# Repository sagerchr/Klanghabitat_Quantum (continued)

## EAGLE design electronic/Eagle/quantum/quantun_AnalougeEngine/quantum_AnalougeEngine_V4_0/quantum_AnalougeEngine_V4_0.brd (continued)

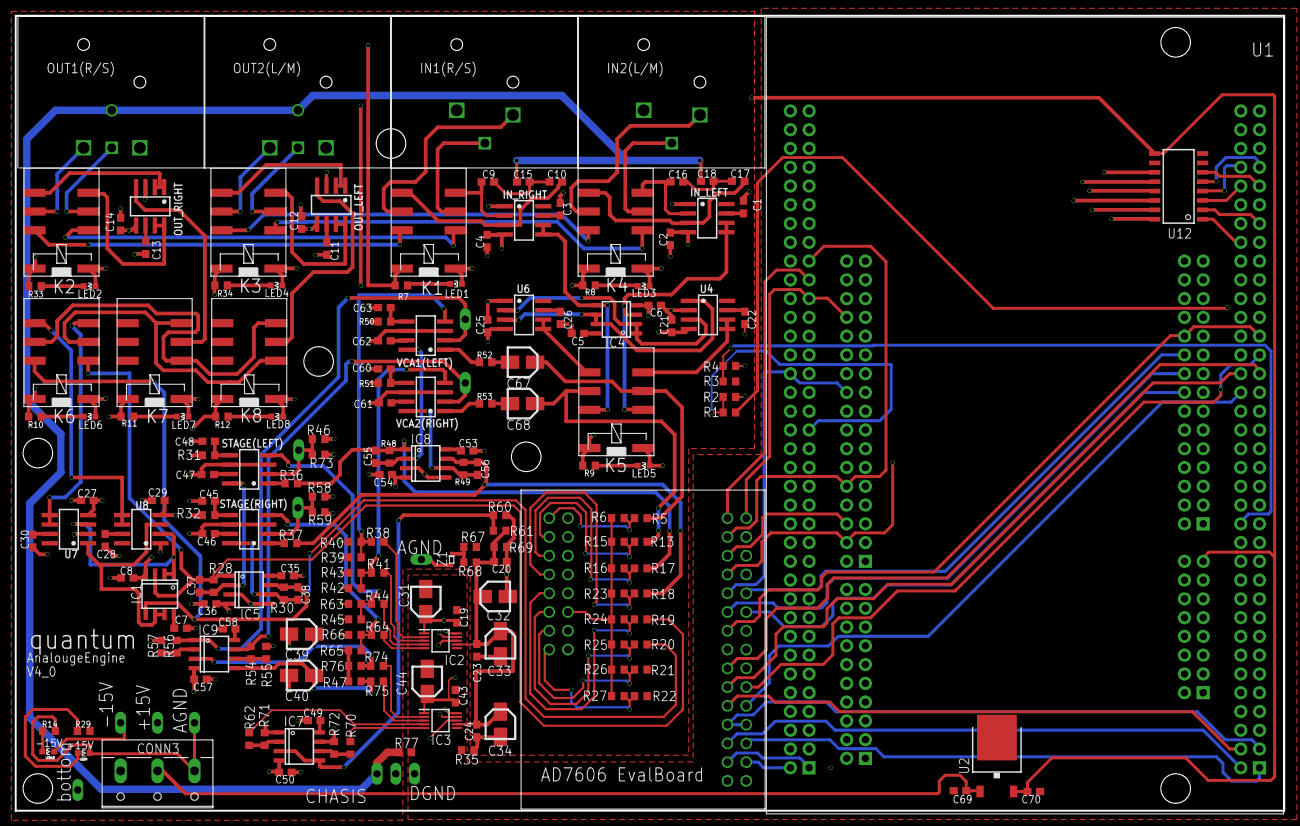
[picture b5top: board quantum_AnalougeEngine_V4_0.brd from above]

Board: 4 copper layers, 171.7 x 107.6 mm, 199 parts (0 on the bottom side), 155 nets.

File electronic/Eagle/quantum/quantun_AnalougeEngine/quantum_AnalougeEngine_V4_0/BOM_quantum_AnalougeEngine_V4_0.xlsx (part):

BOM_quantum_AnalougeEngine_V4_0
BOM_quantum_AnalougeEngine_V4_0
Part | Value | Device | Package | Description | MOUSER_PART_NUMBER | comments
U2 | 7812 | voltage regulator | TO252 |  | 513-NJM7812DL1A-TE1
R35 | 0R | RESISTOR | R0603 | +/- 5 % resistor
R77 | 0R | RESISTOR | R0603 | +/- 5 % resistor
C31 | 10 µF | ELECTROLYTICELCTROLYTIC_MIDSIZE_SMD | CAPAE400X550N | Electrolytic Capacitor SMD
C32 | 10 µF | ELECTROLYTICELCTROLYTIC_MIDSIZE_SMD | CAPAE400X550N | Electrolytic Capacitor SMD
C33 | 10 µF | ELECTROLYTICELCTROLYTIC_MIDSIZE_SMD | CAPAE400X550N | Electrolytic Capacitor SMD
C34 | 10 µF | ELECTROLYTICELCTROLYTIC_MIDSIZE_SMD | CAPAE400X550N | Electrolytic Capacitor SMD
C39 | 10 µF | ELECTROLYTICELCTROLYTIC_MIDSIZE_SMD | CAPAE400X550N | Electrolytic Capacitor SMD
C40 | 10 µF | ELECTROLYTICELCTROLYTIC_MIDSIZE_SMD | CAPAE400X550N | Electrolytic Capacitor SMD
C44 | 10 µF | ELECTROLYTICELCTROLYTIC_MIDSIZE_SMD | CAPAE400X550N | Electrolytic Capacitor SMD
C69 | 100 nF | CAPACITOR";C0603" | capacitor 0603 | ceremic capicitor
R2 | 100k | RESISTOR | R0603 | +/- 5 % resistor
R3 | 100k | RESISTOR | R0603 | +/- 5 % resistor
C1 | 100nF | CAPACITOR";C0603" | capacitor 0603 | ceremic capicitor
C11 | 100nF | CAPACITOR";C0603" | capacitor 0603 | ceremic capicitor
C12 | 100nF | CAPACITOR";C0603" | capacitor 0603 | ceremic capicitor
C13 | 100nF | CAPACITOR";C0603" | capacitor 0603 | ceremic capicitor
C14 | 100nF | CAPACITOR";C0603" | capacitor 0603 | ceremic capicitor
C19 | 100nF | CAPACITOR";C0603" | capacitor 0603 | ceremic capicitor
C2 | 100nF | CAPACITOR";C0603" | capacitor 0603 | ceremic capicitor
C20 | 100nF | CAPACITOR";C0603" | capacitor 0603 | ceremic capicitor
C21 | 100nF | CAPACITOR";C0603" | capacitor 0603 | ceremic capicitor
C22 | 100nF | CAPACITOR";C0603" | capacitor 0603 | ceremic capicitor
C23 | 100nF | CAPACITOR";C0603" | capacitor 0603 | ceremic capicitor
C24 | 100nF | CAPACITOR";C0603" | capacitor 0603 | ceremic capicitor
C25 | 100nF | CAPACITOR";C0603" | capacitor 0603 | ceremic capicitor
C26 | 100nF | CAPACITOR";C0603" | capacitor 0603 | ceremic capicitor
C27 | 100nF | CAPACITOR";C0603" | capacitor 0603 | ceremic capicitor
C28 | 100nF | CAPACITOR";C0603" | capacitor 0603 | ceremic capicitor
C29 | 100nF | CAPACITOR";C0603" | capacitor 0603 | ceremic capicitor
C3 | 100nF | CAPACITOR";C0603" | capacitor 0603 | ceremic capicitor
C30 | 100nF | CAPACITOR";C0603" | capacitor 0603 | ceremic capicitor
C35 | 100nF | CAPACITOR";C0603" | capacitor 0603 | ceremic capicitor
C36 | 100nF | CAPACITOR";C0603" | capacitor 0603 | ceremic capicitor
C4 | 100nF | CAPACITOR";C0603" | capacitor 0603 | ceremic capicitor
C43 | 100nF | CAPACITOR";C0603" | capacitor 0603 | ceremic capicitor
C45 | 100nF | CAPACITOR";C0603" | capacitor 0603 | ceremic capicitor
C46 | 100nF | CAPACITOR";C0603" | capacitor 0603 | ceremic capicitor
C47 | 100nF | CAPACITOR";C0603" | capacitor 0603 | ceremic capicitor
C48 | 100nF | CAPACITOR";C0603" | capacitor 0603 | ceremic capicitor
C49 | 100nF | CAPACITOR";C0603" | capacitor 0603 | ceremic capicitor
C5 | 100nF | CAPACITOR";C0603" | capacitor 0603 | ceremic capicitor
C50 | 100nF | CAPACITOR";C0603" | capacitor 0603 | ceremic capicitor
C53 | 100nF | CAPACITOR";C0603" | capacitor 0603 | ceremic capicitor
C54 | 100nF | CAPACITOR";C0603" | capacitor 0603 | ceremic capicitor
C57 | 100nF | CAPACITOR";C0603" | capacitor 0603 | ceremic capicitor
C58 | 100nF | CAPACITOR";C0603" | capacitor 0603 | ceremic capicitor
C6 | 100nF | CAPACITOR";C0603" | capacitor 0603 | ceremic capicitor
C60 | 100nF | CAPACITOR";C0603" | capacitor 0603 | ceremic capicitor
C61 | 100nF | CAPACITOR";C0603" | capacitor 0603 | ceremic capicitor
C62 | 100nF | CAPACITOR";C0603" | capacitor 0603 | ceremic capicitor
C63 | 100nF | CAPACITOR";C0603" | capacitor 0603 | ceremic capicitor
C7 | 100nF | CAPACITOR";C0603" | capacitor 0603 | ceremic capicitor
C8 | 100nF | CAPACITOR";C0603" | capacitor 0603 | ceremic capicitor
R1 | 10k | RESISTOR | R0603 | +/- 5 % resistor
R13 | 10k | RESISTOR | R0603 | +/- 5 % resistor
R15 | 10k | RESISTOR | R0603 | +/- 5 % resistor
R16 | 10k | RESISTOR | R0603 | +/- 5 % resistor
R17 | 10k | RESISTOR | R0603 | +/- 5 % resistor
R18 | 10k | RESISTOR | R0603 | +/- 5 % resistor
R19 | 10k | RESISTOR | R0603 | +/- 5 % resistor
R20 | 10k | RESISTOR | R0603 | +/- 5 % resistor
R21 | 10k | RESISTOR | R0603 | +/- 5 % resistor
R22 | 10k | RESISTOR | R0603 | +/- 5 % resistor
R23 | 10k | RESISTOR | R0603 | +/- 5 % resistor
R24 | 10k | RESISTOR | R0603 | +/- 5 % resistor
R25 | 10k | RESISTOR | R0603 | +/- 5 % resistor
R26 | 10k | RESISTOR | R0603 | +/- 5 % resistor
R27 | 10k | RESISTOR | R0603 | +/- 5 % resistor
R4 | 10k | RESISTOR | R0603 | +/- 5 % resistor
R46 | 10k | RESISTOR | R0603 | +/- 5 % resistor
R5 | 10k | RESISTOR | R0603 | +/- 5 % resistor
R54 | 10k | RESISTOR | R0603 | +/- 5 % resistor
R55 | 10k | RESISTOR | R0603 | +/- 5 % resistor
R56 | 10k | RESISTOR | R0603 | +/- 5 % resistor
R57 | 10k | RESISTOR | R0603 | +/- 5 % resistor
R58 | 10k | RESISTOR | R0603 | +/- 5 % resistor
R6 | 10k | RESISTOR | R0603 | +/- 5 % resistor
R60 | 10k | RESISTOR | R0603 | +/- 5 % resistor
R61 | 10k | RESISTOR | R0603 | +/- 5 % resistor
R62 | 10k | RESISTOR | R0603 | +/- 5 % resistor
R67 | 10k | RESISTOR | R0603 | +/- 5 % resistor
R68 | 10k | RESISTOR | R0603 | +/- 5 % resistor
R69 | 10k | RESISTOR | R0603 | +/- 5 % resistor
R70 | 10k | RESISTOR | R0603 | +/- 5 % resistor
R71 | 10k | RESISTOR | R0603 | +/- 5 % resistor
R72 | 10k | RESISTOR | R0603 | +/- 5 % resistor
R73 | 10k | RESISTOR | R0603 | +/- 5 % resistor
R74 | 10k | RESISTOR | R0603 | +/- 5 % resistor
R75 | 10k | RESISTOR | R0603 | +/- 5 % resistor
R47 | 1k8 | RESISTOR | R0603 | +/- 5 % resistor
R76 | 1k8 | RESISTOR | R0603 | +/- 5 % resistor
R28 | 20k | RESISTOR | R0603 | +/- 5 % resistor
R30 | 20k | RESISTOR | R0603 | +/- 5 % resistor
R36 | 20k | RESISTOR | R0603 | +/- 5 % resistor
R37 | 20k | RESISTOR | R0603 | +/- 5 % resistor
R48 | 20k | RESISTOR | R0603 | +/- 5 % resistor
R49 | 20k | RESISTOR | R0603 | +/- 5 % resistor
R52 | 20k | RESISTOR | R0603 | +/- 5 % resistor
R53 | 20k | RESISTOR | R0603 | +/- 5 % resistor
R14 | 220R | RESISTOR | R0603 | +/- 5 % resistor
R29 | 220R | RESISTOR | R0603 | +/- 5 % resistor
C37 | 22pF | CAPACITOR";C0603" | capacitor 0603 | ceremic capicitor
C38 | 22pF | CAPACITOR";C0603" | capacitor 0603 | ceremic capicitor
C55 | 22pF | CAPACITOR";C0603" | capacitor 0603 | ceremic capicitor
C56 | 22pF | CAPACITOR";C0603" | capacitor 0603 | ceremic capicitor
C70 | 0,33 uF | CAPACITOR";C0603" | capacitor 0603 | ceremic capicitor
C15 | 47 pF | CAPACITOR";C0603" | capacitor 0603 | ceremic capicitor
C18 | 47 pF | CAPACITOR";C0603" | capacitor 0603 | ceremic capicitor
C10 | 470 pF | CAPACITOR";C0603" | capacitor 0603 | ceremic capicitor
C16 | 470 pF | CAPACITOR";C0603" | capacitor 0603 | ceremic capicitor
C17 | 470 pF | CAPACITOR";C0603" | capacitor 0603 | ceremic capicitor
C9 | 470 pF | CAPACITOR";C0603" | capacitor 0603 | ceremic capicitor
C67 | 47µF | ELECTROLYTICELCTROLYTIC_MIDSIZE_SMD | CAPAE400X550N | Electrolytic Capacitor SMD
C68 | 47µF | ELECTROLYTICELCTROLYTIC_MIDSIZE_SMD | CAPAE400X550N | Electrolytic Capacitor SMD
R10 | 470 R | RESISTOR | R0603 | +/- 5 % resistor
R11 | 470 R | RESISTOR | R0603 | +/- 5 % resistor
R12 | 470 R | RESISTOR | R0603 | +/- 5 % resistor
R33 | 470 R | RESISTOR | R0603 | +/- 5 % resistor
R34 | 470 R | RESISTOR | R0603 | +/- 5 % resistor
R7 | 470 R | RESISTOR | R0603 | +/- 5 % resistor
R8 | 470 R | RESISTOR | R0603 | +/- 5 % resistor
R9 | 470 R | RESISTOR | R0603 | +/- 5 % resistor
R38 | 51k | RESISTOR | R0603 | +/- 5 % resistor
R41 | 51k | RESISTOR | R0603 | +/- 5 % resistor
R44 | 51k | RESISTOR | R0603 | +/- 5 % resistor
R64 | 51k | RESISTOR | R0603 | +/- 5 % resistor
R39 | 51R | RESISTOR | R0603 | +/- 5 % resistor
R42 | 51R | RESISTOR | R0603 | +/- 5 % resistor
R45 | 51R | RESISTOR | R0603 | +/- 5 % resistor
R65 | 51R | RESISTOR | R0603 | +/- 5 % resistor
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
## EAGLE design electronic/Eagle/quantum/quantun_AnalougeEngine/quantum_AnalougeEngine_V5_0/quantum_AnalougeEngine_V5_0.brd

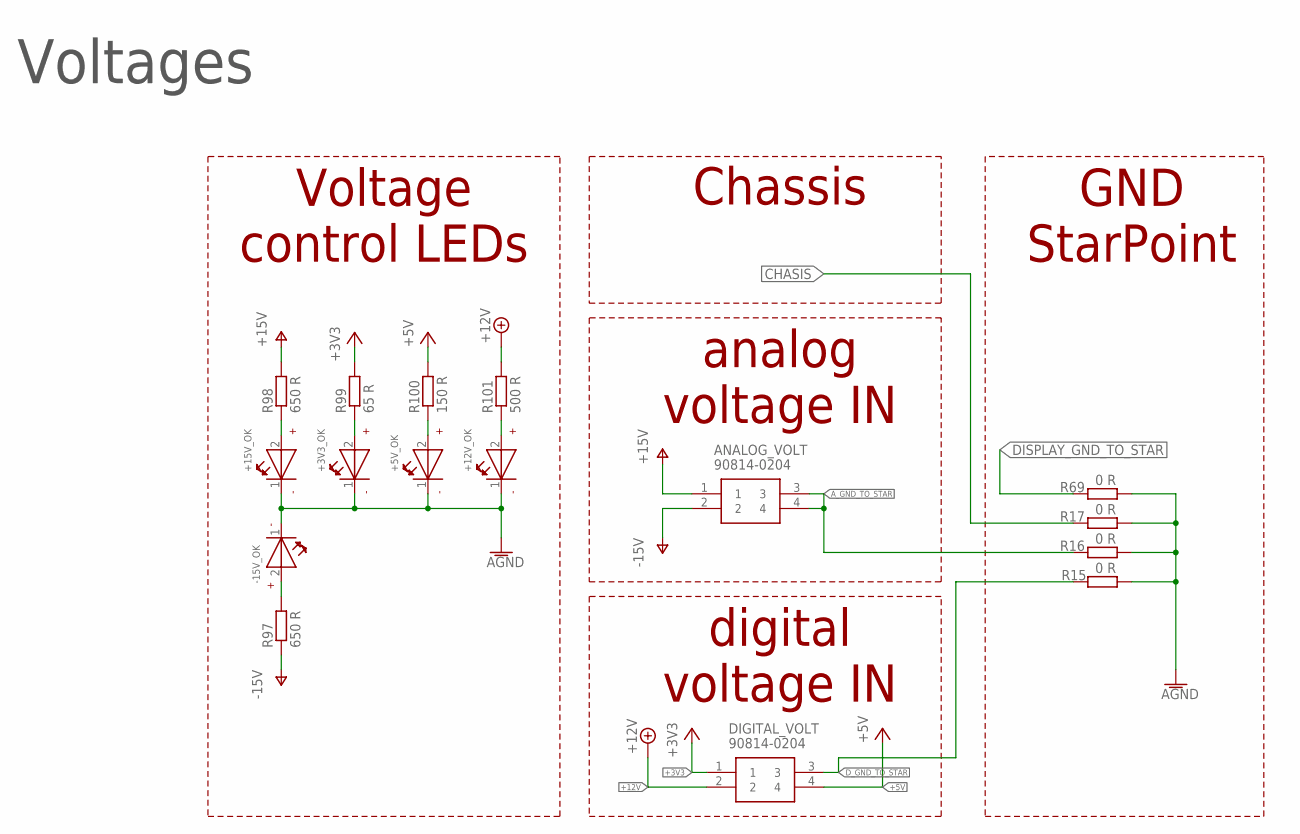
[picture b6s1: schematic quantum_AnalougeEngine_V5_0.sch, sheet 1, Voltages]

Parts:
+3V3_OK, +5V_OK, +12V_OK, +15V_OK: LED_GREEN_SMD; WL-SMCW_0603
-15V_OK: LED_GREEN_SMD; WL-SMCW_0603
ANALOG_VOLT: 90814-0204; MOLEX_90814-0204
DIGITAL_VOLT: 90814-0204; MOLEX_90814-0204
R15, R16, R17, R69: 0 R; R0603
R97, R98: 650 R; R0603
R99: 65 R; R0603
R100: 150 R; R0603
R101: 500 R; R0603

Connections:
+3V3: DIGITAL_VOLT.1, R99.2; also elsewhere on the board
+5V: DIGITAL_VOLT.4, R100.2; also elsewhere on the board
+12V: DIGITAL_VOLT.2, R101.2; also elsewhere on the board
AGND: +3V3_OK.1 (-), +5V_OK.1 (-), +12V_OK.1 (-), +15V_OK.1 (-), -15V_OK.1 (-), R15.2, R16.2, R17.2, R69.2; also elsewhere on the board
A_GND_TO_STAR: ANALOG_VOLT.3, ANALOG_VOLT.4, R16.1; also elsewhere on the board
CHASIS: R17.1; also elsewhere on the board
DISPLAY_GND_TO_STAR: R69.1; also elsewhere on the board
D_GND_TO_STAR: DIGITAL_VOLT.3, R15.1
unnamed: -15V_OK.2 (+), R97.2
unnamed: +15V_OK.2 (+), R98.1
unnamed: +3V3_OK.2 (+), R99.1
unnamed: +5V_OK.2 (+), R100.1
unnamed: +12V_OK.2 (+), R101.1
V+: ANALOG_VOLT.1, R98.2; also elsewhere on the board
V-: ANALOG_VOLT.2, R97.1; also elsewhere on the board

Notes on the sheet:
analog voltage IN
digital voltage IN
GND StarPoint
Chassis
Voltages
Voltage control LEDs

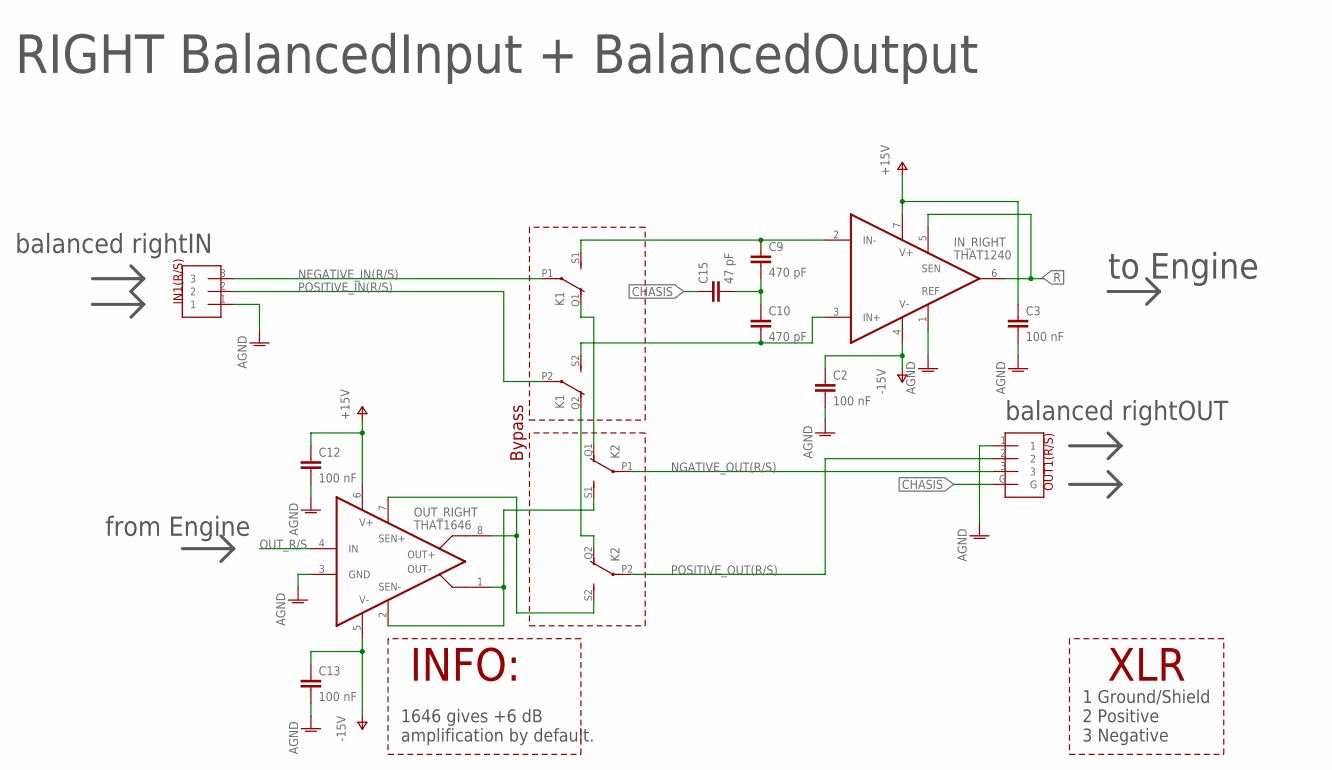
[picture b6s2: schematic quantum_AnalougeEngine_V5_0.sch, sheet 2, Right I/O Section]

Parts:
C2, C3, C12, C13: 100 nF; C0603
C9, C10: 470 pF; C0603
C15: 47 pF; C0603
IN1(R/S): NEUTRIK_NC3FAH
IN_RIGHT: THAT1240; SO08
K1, K2: Relay; 351
OUT1(R/S): NEUTRIK_NC3MAH
OUT_RIGHT: THAT1646; SO08

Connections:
AGND: C2.2, C3.2, C12.2, C13.2, IN1(R/S).1, IN_RIGHT.1 (REF), OUT1(R/S).1, OUT_RIGHT.3 (GND); also elsewhere on the board
CHASIS: C15.1, OUT1(R/S).G; also elsewhere on the board
unnamed: C9.1, IN_RIGHT.2 (IN-), K1.S1 (S)
unnamed: C10.2, IN_RIGHT.3 (IN+), K1.S2 (S)
unnamed: C9.2, C10.1, C15.2
unnamed: K1.Q1 (O), K2.Q1 (O)
unnamed: K1.Q2 (O), K2.Q2 (O)
NEGATIVE_IN(R/S): IN1(R/S).3, K1.P1
NGATIVE_OUT(R/S): K2.P1, OUT1(R/S).3
OUT_R/S: OUT_RIGHT.4 (IN); also elsewhere on the board
POSITIVE_IN(R/S): IN1(R/S).2, K1.P2
POSITIVE_OUT(R/S): K2.P2, OUT1(R/S).2
R: IN_RIGHT.5 (SEN), IN_RIGHT.6 (OUT); also elsewhere on the board
R/S_OUT+: K2.S2 (S), OUT_RIGHT.7 (SEN+), OUT_RIGHT.8 (OUT+)
R/S_OUT-: K2.S1 (S), OUT_RIGHT.1 (OUT-), OUT_RIGHT.2 (SEN-)
V+: C3.1, C12.1, IN_RIGHT.7 (V+), OUT_RIGHT.6 (V+); also elsewhere on the board
V-: C2.1, C13.1, IN_RIGHT.4 (V-), OUT_RIGHT.5 (V-); also elsewhere on the board

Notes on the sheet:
RIGHT BalancedInput + BalancedOutput
balanced rightIN
balanced rightOUT
from Engine
to Engine
XLR
1 Ground/Shield 2 Positive 3 Negative
INFO:
1646 gives +6 dB amplification by default.
Bypass

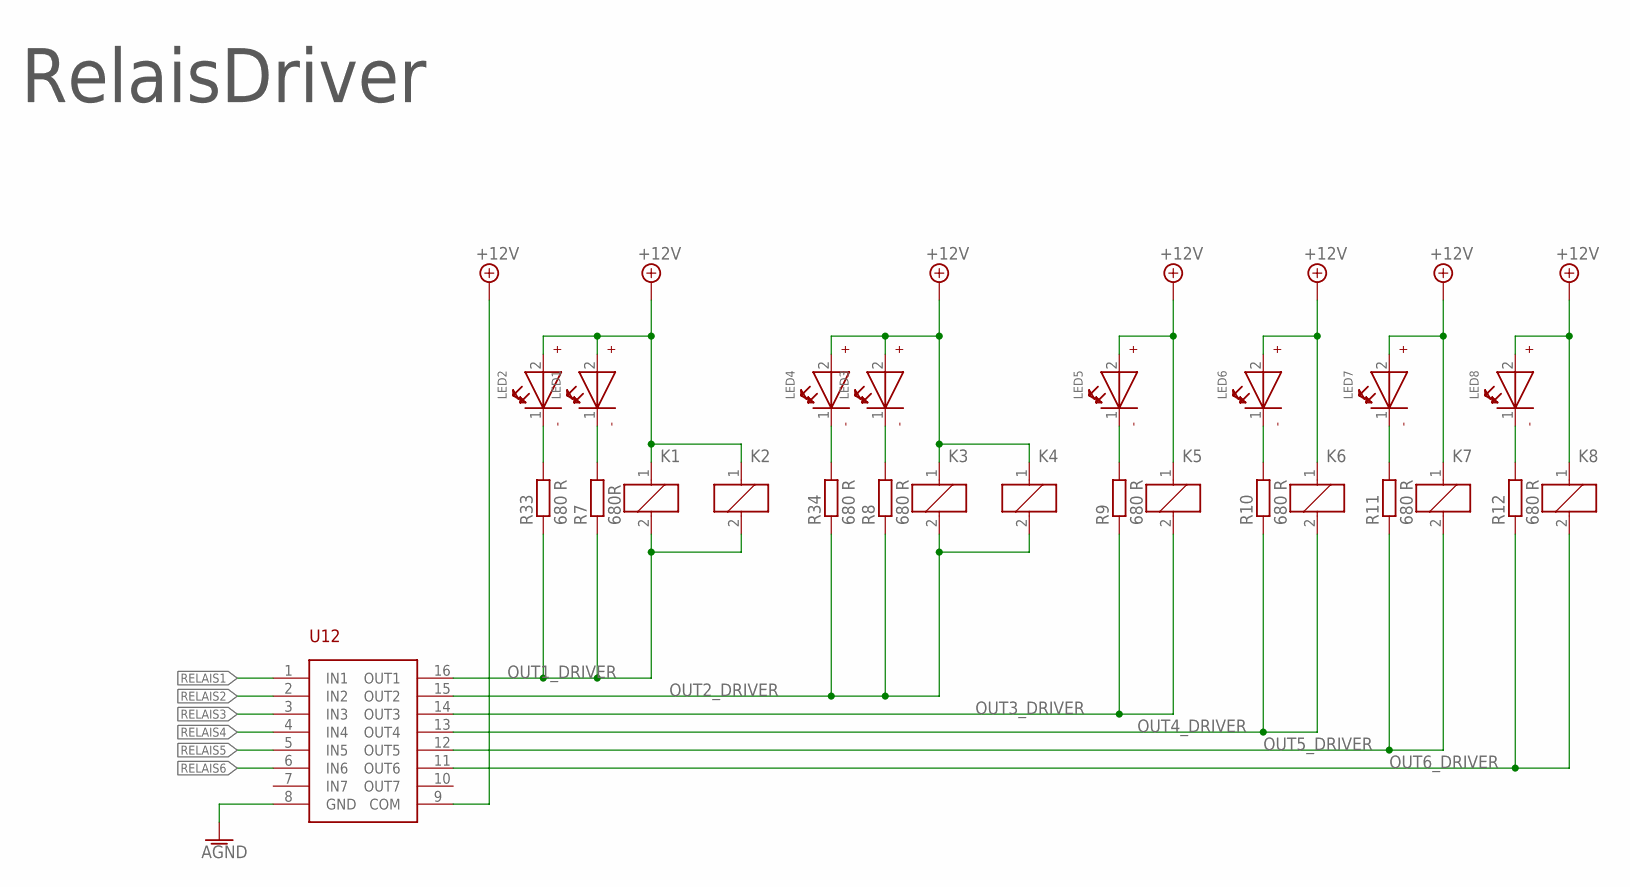
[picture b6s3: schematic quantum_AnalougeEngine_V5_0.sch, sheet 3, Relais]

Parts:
K1, K2, K3, K4, K5, K6, K7, K8: Relay; 351
LED1, LED2, LED3, LED4, LED5, LED6, LED7, LED8: LED_BLUE_SMD; WL-SMCW_0603
R7: 680R; R0603
R8, R9, R10, R11, R12, R33, R34: 680 R; R0603
U12: ULN2003; SOIC16

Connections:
+12V: K1.1, K2.1, K3.1, K4.1, K5.1, K6.1, K7.1, K8.1, LED1.2 (+), LED2.2 (+), LED3.2 (+), LED4.2 (+), LED5.2 (+), LED6.2 (+), LED7.2 (+), LED8.2 (+), U12.9 (COM); also elsewhere on the board
AGND: U12.8 (GND); also elsewhere on the board
unnamed: LED1.1 (-), R7.2
unnamed: LED3.1 (-), R8.2
unnamed: LED8.1 (-), R12.2
unnamed: LED7.1 (-), R11.2
unnamed: LED6.1 (-), R10.2
unnamed: LED5.1 (-), R9.2
unnamed: LED2.1 (-), R33.2
unnamed: LED4.1 (-), R34.2
OUT1_DRIVER: K1.2, K2.2, R7.1, R33.1, U12.16 (OUT1)
OUT2_DRIVER: K3.2, K4.2, R8.1, R34.1, U12.15 (OUT2)
OUT3_DRIVER: K5.2, R9.1, U12.14 (OUT3)
OUT4_DRIVER: K6.2, R10.1, U12.13 (OUT4)
OUT5_DRIVER: K7.2, R11.1, U12.12 (OUT5)
OUT6_DRIVER: K8.2, R12.1, U12.11 (OUT6)
RELAIS1: U12.1 (IN1); also elsewhere on the board
RELAIS2: U12.2 (IN2); also elsewhere on the board
RELAIS3: U12.3 (IN3); also elsewhere on the board
RELAIS4: U12.4 (IN4); also elsewhere on the board
RELAIS5: U12.5 (IN5); also elsewhere on the board
RELAIS6: U12.6 (IN6); also elsewhere on the board

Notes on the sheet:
RelaisDriver

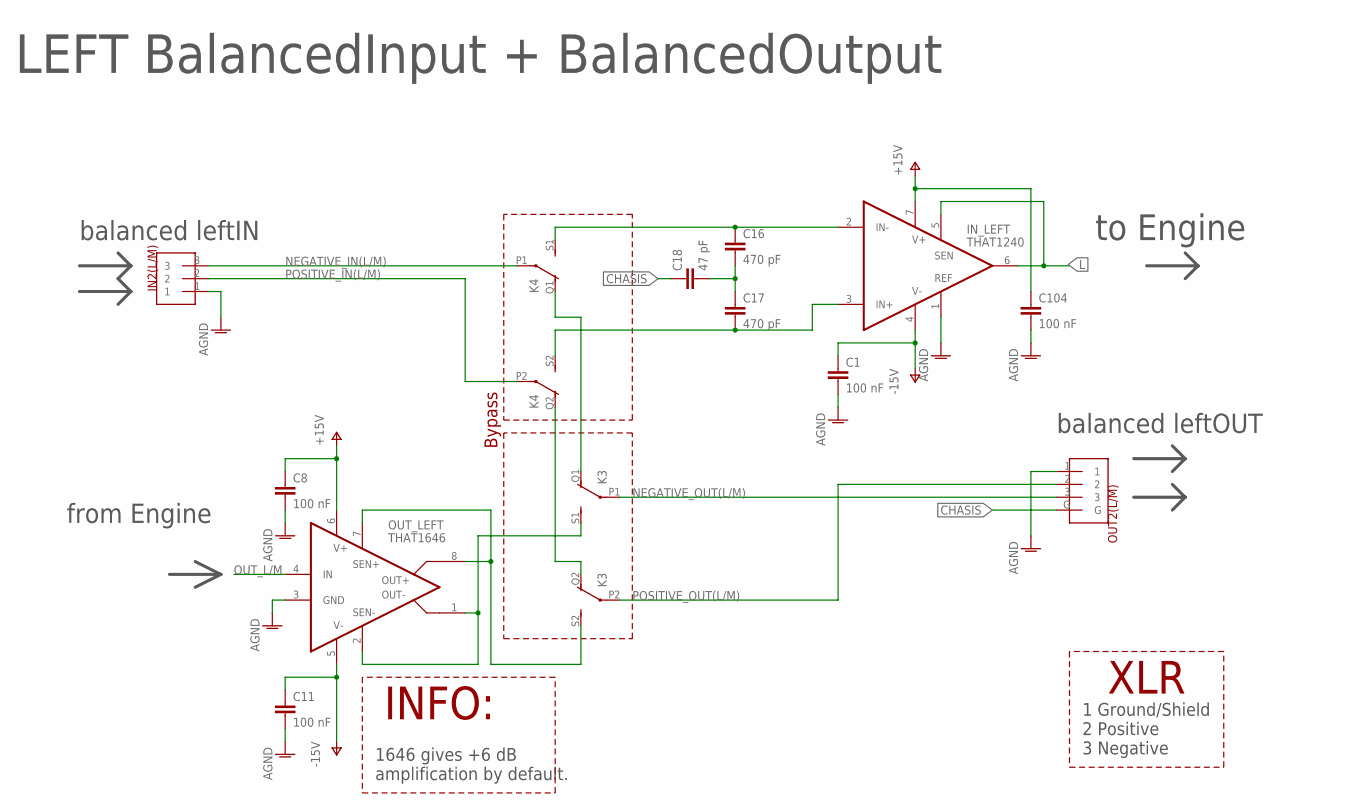
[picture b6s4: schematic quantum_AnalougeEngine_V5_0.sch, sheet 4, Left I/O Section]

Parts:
C1, C8, C11, C104: 100 nF; C0603
C16, C17: 470 pF; C0603
C18: 47 pF; C0603
IN2(L/M): NEUTRIK_NC3FAH
IN_LEFT: THAT1240; SO08
K3, K4: Relay; 351
OUT2(L/M): NEUTRIK_NC3MAH
OUT_LEFT: THAT1646; SO08

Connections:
AGND: C1.2, C8.2, C11.2, C104.2, IN2(L/M).1, IN_LEFT.1 (REF), OUT2(L/M).1, OUT_LEFT.3 (GND); also elsewhere on the board
CHASIS: C18.1, OUT2(L/M).G; also elsewhere on the board
L: IN_LEFT.5 (SEN), IN_LEFT.6 (OUT); also elsewhere on the board
L/M_OUT+: K3.S2 (S), OUT_LEFT.7 (SEN+), OUT_LEFT.8 (OUT+)
L/M_OUT-: K3.S1 (S), OUT_LEFT.1 (OUT-), OUT_LEFT.2 (SEN-)
unnamed: C17.2, IN_LEFT.3 (IN+), K4.S2 (S)
unnamed: C16.2, C17.1, C18.2
unnamed: C16.1, IN_LEFT.2 (IN-), K4.S1 (S)
unnamed: K3.Q1 (O), K4.Q1 (O)
unnamed: K3.Q2 (O), K4.Q2 (O)
NEGATIVE_IN(L/M): IN2(L/M).3, K4.P1
NEGATIVE_OUT(L/M): K3.P1, OUT2(L/M).3
OUT_L/M: OUT_LEFT.4 (IN); also elsewhere on the board
POSITIVE_IN(L/M): IN2(L/M).2, K4.P2
POSITIVE_OUT(L/M): K3.P2, OUT2(L/M).2
V+: C8.1, C104.1, IN_LEFT.7 (V+), OUT_LEFT.6 (V+); also elsewhere on the board
V-: C1.1, C11.1, IN_LEFT.4 (V-), OUT_LEFT.5 (V-); also elsewhere on the board

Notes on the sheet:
balanced leftIN
balanced leftOUT
from Engine
to Engine
LEFT BalancedInput + BalancedOutput
XLR
1 Ground/Shield 2 Positive 3 Negative
INFO:
1646 gives +6 dB amplification by default.
Bypass

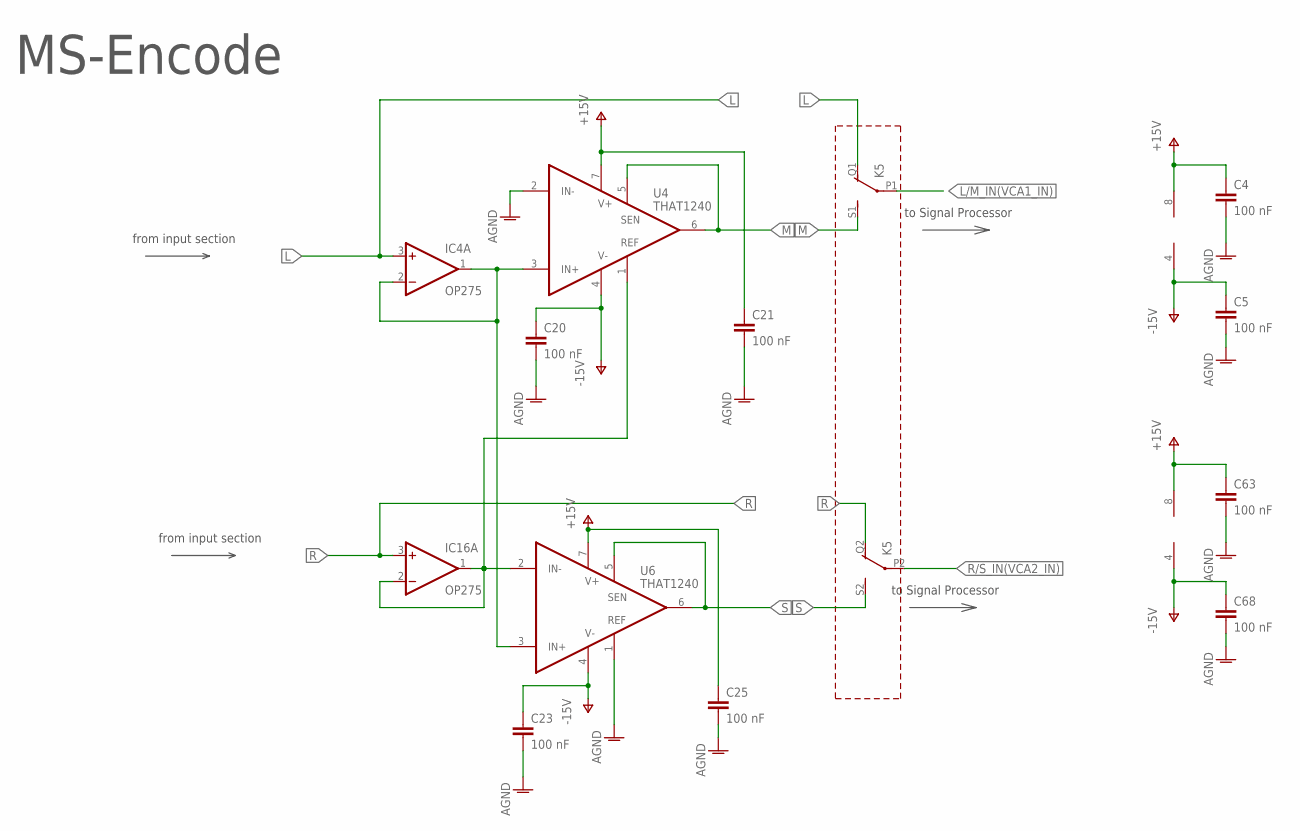
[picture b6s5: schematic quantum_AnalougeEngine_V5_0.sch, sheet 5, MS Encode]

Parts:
C4, C5, C20, C21, C23, C25, C63, C68: 100 nF; C0603
IC4, IC16: OP275; SOIC8
K5: Relay; 351
U4, U6: THAT1240; SO08

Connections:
AGND: C4.2, C5.2, C20.2, C21.2, C23.2, C25.2, C63.2, C68.2, U4.2 (IN-), U6.1 (REF); also elsewhere on the board
L: IC4.3 (+IN), K5.Q1 (O); also elsewhere on the board
L/M_IN(VCA1_IN): K5.P1; also elsewhere on the board
M: K5.S1 (S), U4.5 (SEN), U4.6 (OUT)
unnamed: IC4.1 (OUT), IC4.2 (-IN), U4.3 (IN+), U6.3 (IN+)
unnamed: IC16.1 (OUT), IC16.2 (-IN), U4.1 (REF), U6.2 (IN-)
R: IC16.3 (+IN), K5.Q2 (O); also elsewhere on the board
R/S_IN(VCA2_IN): K5.P2; also elsewhere on the board
S: K5.S2 (S), U6.5 (SEN), U6.6 (OUT)
V+: C4.1, C21.1, C25.1, C63.1, IC4.8 (V+), IC16.8 (V+), U4.7 (V+), U6.7 (V+); also elsewhere on the board
V-: C5.1, C20.1, C23.1, C68.1, IC4.4 (V-), IC16.4 (V-), U4.4 (V-), U6.4 (V-); also elsewhere on the board

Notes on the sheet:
to Signal Processor
MS-Encode
from input section

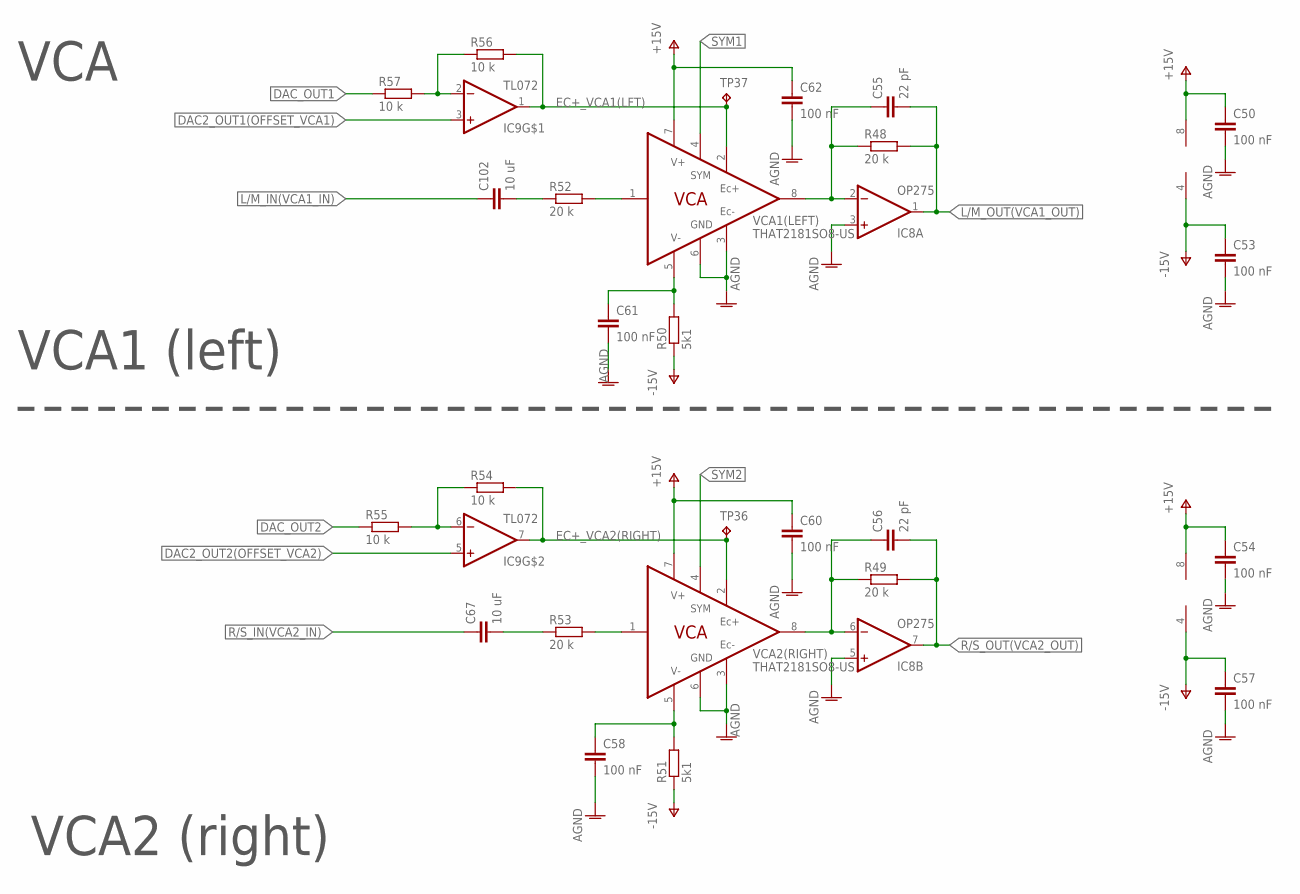
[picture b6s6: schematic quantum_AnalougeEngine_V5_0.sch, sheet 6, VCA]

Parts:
C50, C53, C54, C57, C58, C60, C61, C62: 100 nF; C0603
C55, C56: 22 pF; C0603
C67, C102: 10 uF; C1206
IC8: OP275; SOIC8
IC9: TL072; SOIC8
R48, R49, R52, R53: 20 k; R0603
R50, R51: 5k1; R0603
R54, R55, R56, R57: 10 k; R0603
TP36, TP37: TPTHT; THT_PIN
VCA1(LEFT), VCA2(RIGHT): THAT2181SO8-US; SO08

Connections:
AGND: C50.2, C53.2, C54.2, C57.2, C58.2, C60.2, C61.2, C62.2, IC8.3 (+IN), IC8.5 (+IN), VCA1(LEFT).3 (EC-), VCA1(LEFT).6 (GND), VCA2(RIGHT).3 (EC-), VCA2(RIGHT).6 (GND); also elsewhere on the board
DAC2_OUT1(OFFSET_VCA1): IC9.3 (+IN); also elsewhere on the board
DAC2_OUT2(OFFSET_VCA2): IC9.5 (+IN); also elsewhere on the board
DAC_OUT1: R57.1; also elsewhere on the board
DAC_OUT2: R55.1; also elsewhere on the board
EC+_VCA1(LFT): IC9.1 (OUT), R56.2, TP37.P$1, VCA1(LEFT).2 (EC+)
EC+_VCA2(RIGHT): IC9.7 (OUT), R54.2, TP36.P$1, VCA2(RIGHT).2 (EC+)
L/M_IN(VCA1_IN): C102.1; also elsewhere on the board
L/M_OUT(VCA1_OUT): C55.2, IC8.1 (OUT), R48.2; also elsewhere on the board
unnamed: IC9.2 (-IN), R56.1, R57.2
unnamed: C55.1, IC8.2 (-IN), R48.1, VCA1(LEFT).8 (OUT)
unnamed: R52.2, VCA1(LEFT).1 (IN)
unnamed: C102.2, R52.1
unnamed: C56.1, IC8.6 (-IN), R49.1, VCA2(RIGHT).8 (OUT)
unnamed: C58.1, R51.2, VCA2(RIGHT).5 (V-)
unnamed: C67.2, R53.1
unnamed: R53.2, VCA2(RIGHT).1 (IN)
unnamed: C61.1, R50.2, VCA1(LEFT).5 (V-)
unnamed: IC9.6 (-IN), R54.1, R55.2
R/S_IN(VCA2_IN): C67.1; also elsewhere on the board
R/S_OUT(VCA2_OUT): C56.2, IC8.7 (OUT), R49.2; also elsewhere on the board
SYM1: VCA1(LEFT).4 (SYM); also elsewhere on the board
SYM2: VCA2(RIGHT).4 (SYM); also elsewhere on the board
V+: C50.1, C54.1, C60.1, C62.1, IC8.8 (V+), IC9.8 (V+), VCA1(LEFT).7 (V+), VCA2(RIGHT).7 (V+); also elsewhere on the board
V-: C53.1, C57.1, IC8.4 (V-), IC9.4 (V-), R50.1, R51.1; also elsewhere on the board

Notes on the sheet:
VCA
VCA1 (left)
VCA2 (right)

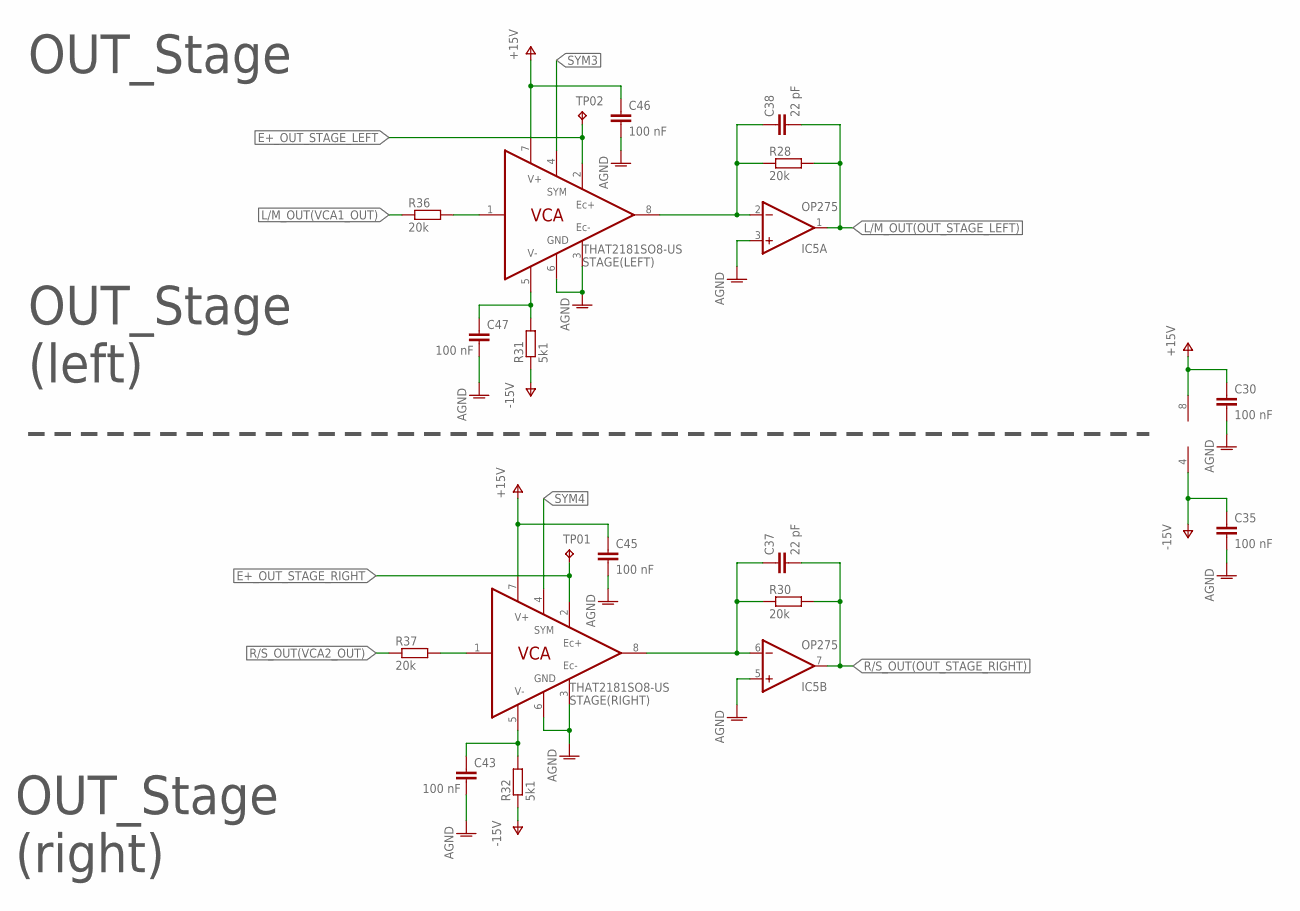
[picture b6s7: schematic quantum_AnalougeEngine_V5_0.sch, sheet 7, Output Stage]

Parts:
C30, C35, C43, C45, C46, C47: 100 nF; C0603
C37, C38: 22 pF; C0603
IC5: OP275; SOIC8
R28, R30, R36, R37: 20k; R0603
R31, R32: 5k1; R0603
STAGE(LEFT): THAT2181SO8-US; SO08
STAGE(RIGHT): THAT2181SO8-US; SO08
TP01, TP02: TPTHT; THT_PIN

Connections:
AGND: C30.2, C35.2, C43.2, C45.2, C46.2, C47.2, IC5.3 (+IN), IC5.5 (+IN), STAGE(LEFT).3 (EC-), STAGE(LEFT).6 (GND), STAGE(RIGHT).3 (EC-), STAGE(RIGHT).6 (GND); also elsewhere on the board
E+_OUT_STAGE_LEFT: STAGE(LEFT).2 (EC+), TP02.P$1; also elsewhere on the board
E+_OUT_STAGE_RIGHT: STAGE(RIGHT).2 (EC+), TP01.P$1; also elsewhere on the board
L/M_OUT(OUT_STAGE_LEFT)_BEFORE: C38.2, IC5.1 (OUT), R28.2; also elsewhere on the board
unnamed: C38.1, IC5.2 (-IN), R28.1, STAGE(LEFT).8 (OUT)
unnamed: C37.1, IC5.6 (-IN), R30.1, STAGE(RIGHT).8 (OUT)
unnamed: C43.1, R32.2, STAGE(RIGHT).5 (V-)
unnamed: R36.2, STAGE(LEFT).1 (IN)
unnamed: R37.2, STAGE(RIGHT).1 (IN)
unnamed: C47.1, R31.2, STAGE(LEFT).5 (V-)
unnamed 169: R37.1; also elsewhere on the board
unnamed 170: R36.1; also elsewhere on the board
R/S_OUT(OUT_STAGE_RIGHT)_BEFORE: C37.2, IC5.7 (OUT), R30.2; also elsewhere on the board
SYM3: STAGE(LEFT).4 (SYM); also elsewhere on the board
SYM4: STAGE(RIGHT).4 (SYM); also elsewhere on the board
V+: C30.1, C45.1, C46.1, IC5.8 (V+), STAGE(LEFT).7 (V+), STAGE(RIGHT).7 (V+); also elsewhere on the board
V-: C35.1, IC5.4 (V-), R31.1, R32.1; also elsewhere on the board

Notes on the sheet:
OUT_Stage
OUT_Stage (left)
OUT_Stage (right)

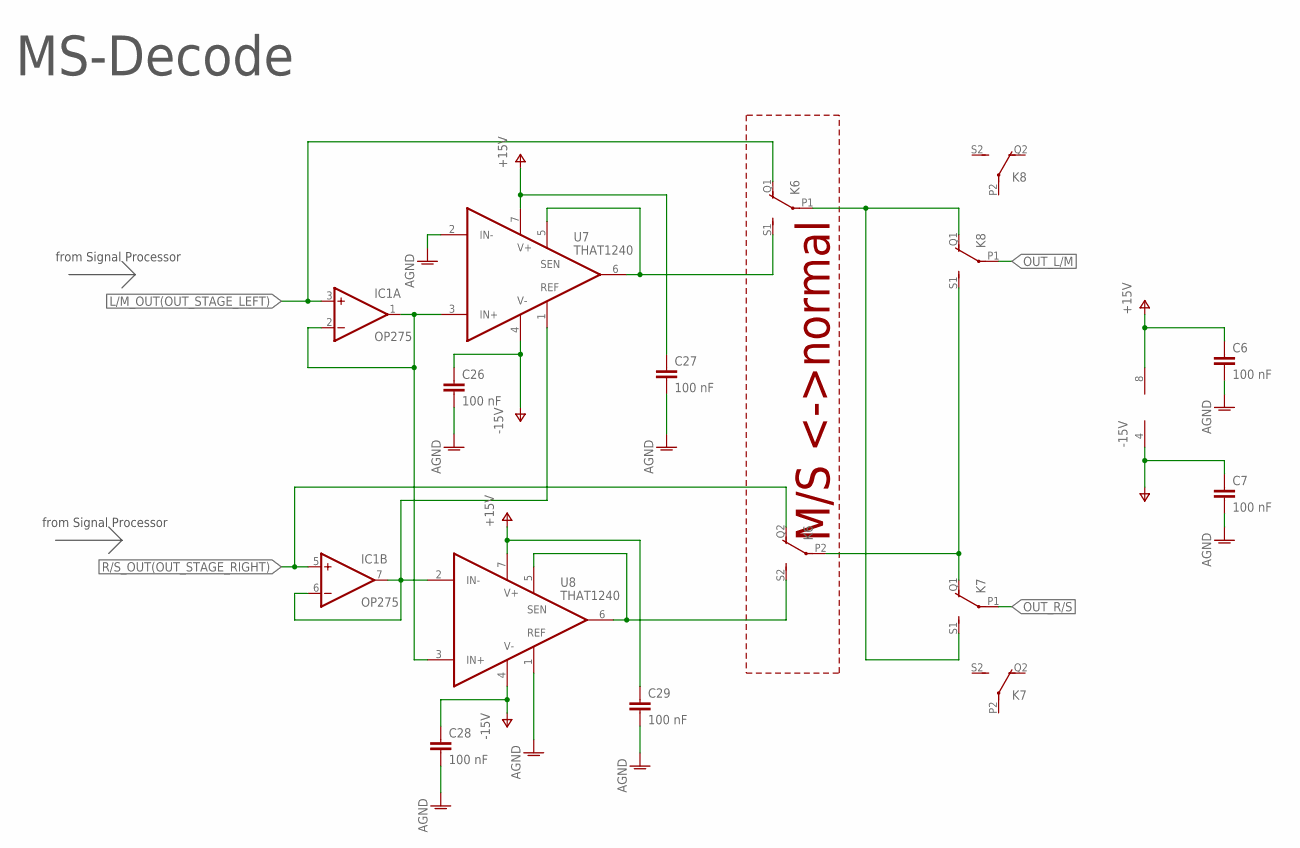
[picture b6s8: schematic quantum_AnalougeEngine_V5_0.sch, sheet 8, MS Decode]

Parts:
C6, C7, C26, C27, C28, C29: 100 nF; C0603
IC1: OP275; SOIC8
K6, K7, K8: Relay; 351
U7, U8: THAT1240; SO08

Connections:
AGND: C6.2, C7.2, C26.2, C27.2, C28.2, C29.2, U7.2 (IN-), U8.1 (REF); also elsewhere on the board
L/M_OUT(OUT_STAGE_LEFT): IC1.3 (+IN), K6.Q1 (O); also elsewhere on the board
M1: K6.S1 (S), U7.5 (SEN), U7.6 (OUT)
unnamed: K6.P1, K7.S1 (S), K8.Q1 (O)
unnamed: K6.P2, K7.Q1 (O), K8.S1 (S)
unnamed: IC1.6 (-IN), IC1.7 (OUT), U7.1 (REF), U8.2 (IN-)
unnamed: IC1.1 (OUT), IC1.2 (-IN), U7.3 (IN+), U8.3 (IN+)
OUT_L/M: K8.P1; also elsewhere on the board
OUT_R/S: K7.P1; also elsewhere on the board
R/S_OUT(OUT_STAGE_RIGHT): IC1.5 (+IN), K6.Q2 (O); also elsewhere on the board
S1: K6.S2 (S), U8.5 (SEN), U8.6 (OUT)
V+: C6.1, C27.1, C29.1, IC1.8 (V+), U7.7 (V+), U8.7 (V+); also elsewhere on the board
V-: C7.1, C26.1, C28.1, IC1.4 (V-), U7.4 (V-), U8.4 (V-); also elsewhere on the board

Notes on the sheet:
from Signal Processor
MS-Decode
M/S <->normal
